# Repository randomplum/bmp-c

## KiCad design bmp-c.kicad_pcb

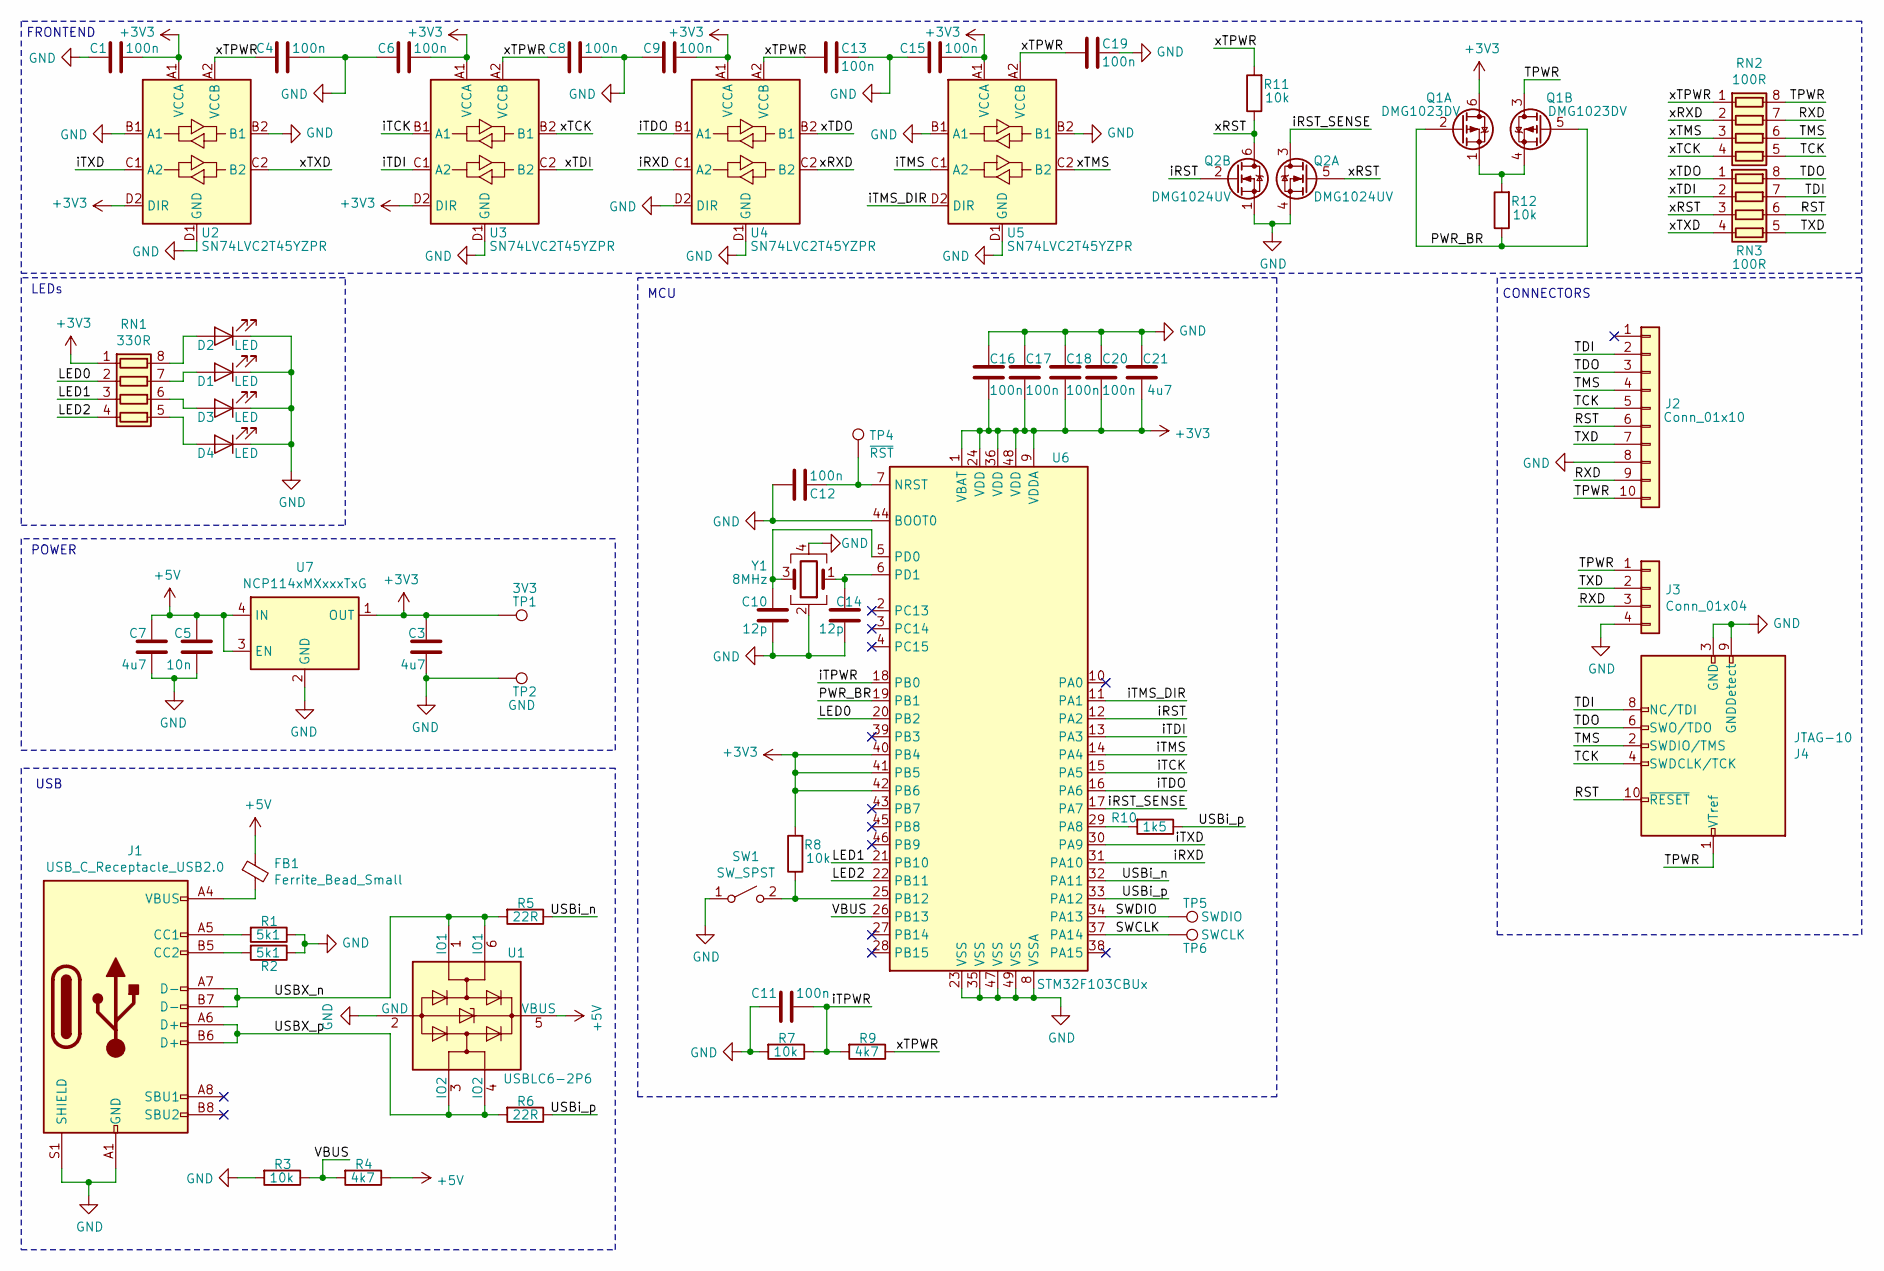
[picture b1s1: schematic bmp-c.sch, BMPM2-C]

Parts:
C1, C4, C6, C8, C9, C11, C12, C13, C15, C16, C17, C18, C19, C20: 100n; C_0402_1005Metric
C3, C7, C21: 4u7; C_0603_1608Metric
C5: 10n; C_0402_1005Metric
C10, C14: 12p; C_0402_1005Metric
D1, D2, D3, D4: LED; LED_0402_1005Metric
FB1: Ferrite_Bead_Small; Fuse_0603_1608Metric
J1: USB_C_Receptacle_USB2.0; USB_C_Receptacle_HRO_TYPE-C-31-M-12
J2: Conn_01x10; Hirose_FH12-10S-0.5SH_1x10-1MP_P0.50mm_Horizontal
J3: Conn_01x04; JST_SH_SM04B-SRSS-TB_1x04-1MP_P1.00mm_Horizontal
J4: JTAG-10; PinHeader_2x05_P1.27mm_Vertical_SMD
Q1: DMG1023DV; SOT-563
Q2: DMG1024UV; SOT-563
R1, R2: 5k1; R_0402_1005Metric
R3, R7, R8, R11, R12: 10k; R_0402_1005Metric
R4, R9: 4k7; R_0402_1005Metric
R5, R6: 22R; R_0402_1005Metric
R10: 1k5; R_0402_1005Metric
RN1: 330R; R_Array_Convex_4x0402
RN2, RN3: 100R; R_Array_Convex_4x0402
SW1: SW_SPST; SW_SPST_B3U-1000P
TP1: 3V3; TestPoint_Pad_D1.0mm
TP2: GND; TestPoint_Pad_D1.0mm
TP4: ~RST; TestPoint_Pad_D1.0mm
TP5: SWDIO; TestPoint_Pad_D1.0mm
TP6: SWCLK; TestPoint_Pad_D1.0mm
U1: USBLC6-2P6; SOT-666
U2, U3, U4, U5: SN74LVC2T45YZPR; Texas_DSBGA-8_0.9x1.9mm_Layout2x4_P0.5mm
U6: STM32F103CBUx; QFN-48-1EP_7x7mm_P0.5mm_EP5.3x5.3mm_ThermalVias
U7: NCP114xMXxxxTxG; UDFN-4_1x1mm_P0.65mm
Y1: 8MHz; Crystal_SMD_3225-4Pin_3.2x2.5mm

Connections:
+3V3: C1.1, C3.1, C6.1, C9.1, C15.1, C16.2, C17.2, C18.2, C20.2, C21.2, Q1.6 (D), R8.2, RN1.1 (R1.1), TP1.1, U2.A1 (VCCA), U2.D2 (DIR), U3.A1 (VCCA), U3.D2 (DIR), U4.A1 (VCCA), U5.A1 (VCCA), U6.1 (VBAT), U6.9 (VDDA), U6.24 (VDD), U6.36 (VDD), U6.40 (PB4), U6.41 (PB5), U6.42 (PB6), U6.48 (VDD), U7.1 (OUT)
+5V: C5.1, C7.1, FB1.1, R4.1, U1.5 (VBUS), U7.3 (EN), U7.4 (IN)
/LED0: RN1.2 (R2.1), U6.20 (PB2)
/LED1: RN1.3 (R3.1), U6.21 (PB10)
/LED2: RN1.4 (R4.1), U6.22 (PB11)
/PWR_BR: Q1.2 (G), Q1.5 (G), R12.1, U6.19 (PB1)
/RST: J2.6, J4.10 (~RESET~), RN3.6 (R3.2)
/RXD: J2.9, J3.3, RN2.7 (R2.2)
/SWCLK: TP6.1, U6.37 (PA14)
/SWDIO: TP5.1, U6.34 (PA13)
/TCK: J2.5, J4.4 (SWDCLK/TCK), RN2.5 (R4.2)
/TDI: J2.2, J4.8 (NC/TDI), RN3.7 (R2.2)
/TDO: J2.3, J4.6 (SWO/TDO), RN3.8 (R1.2)
/TMS: J2.4, J4.2 (SWDIO/TMS), RN2.6 (R3.2)
/TPWR: J2.10, J3.1, J4.1 (VTref), Q1.3 (D), RN2.8 (R1.2)
/TXD: J2.7, J3.2, RN3.5 (R4.2)
/USBX_n: J1.A7 (D-), J1.B7 (D-), R5.2, U1.1 (IO1), U1.6 (IO1)
/USBX_p: J1.A6 (D+), J1.B6 (D+), R6.2, U1.3 (IO2), U1.4 (IO2)
/USBi_n: R5.1, U6.32 (PA11)
/USBi_p: R6.1, R10.1, U6.33 (PA12)
/VBUS: R3.1, R4.2, U6.26 (PB13)
/iRST: Q2.2 (G), U6.12 (PA2)
/iRST_SENSE: Q2.3 (D), U6.17 (PA7)
/iRXD: U4.C1 (A2), U6.31 (PA10)
/iTCK: U3.B1 (A1), U6.15 (PA5)
/iTDI: U3.C1 (A2), U6.13 (PA3)
/iTDO: U4.B1 (A1), U6.16 (PA6)
/iTMS: U5.C1 (A2), U6.14 (PA4)
/iTMS_DIR: U5.D2 (DIR), U6.11 (PA1)
/iTPWR: C11.1, R7.1, R9.2, U6.18 (PB0)
/iTXD: U2.C1 (A2), U6.30 (PA9)
/xRST: Q2.5 (G), Q2.6 (D), R11.1, RN3.3 (R3.1)
/xRXD: RN2.2 (R2.1), U4.C2 (B2)
/xTCK: RN2.4 (R4.1), U3.B2 (B1)
/xTDI: RN3.2 (R2.1), U3.C2 (B2)
/xTDO: RN3.1 (R1.1), U4.B2 (B1)
/xTMS: RN2.3 (R3.1), U5.C2 (B2)
/xTPWR: C4.2, C8.2, C13.2, C19.2, R9.1, R11.2, RN2.1 (R1.1), U2.A2 (VCCB), U3.A2 (VCCB), U4.A2 (VCCB), U5.A2 (VCCB)
/xTXD: RN3.4 (R4.1), U2.C2 (B2)
GND: C1.2, C3.2, C4.1, C5.2, C6.2, C7.2, C8.1, C9.2, C10.1, C11.2, C12.2, C13.1, C14.1, C15.2, C16.1, C17.1, C18.1, C19.1, C20.1, C21.1, D1.1 (K), D2.1 (K), D3.1 (K), D4.1 (K), J1.A1 (GND), J1.A12 (GND), J1.B1 (GND), J1.B12 (GND), J1.S1 (SHIELD), J2.8, J3.4, J4.3 (GND), J4.5 (GND), J4.9 (GNDDetect), Q2.1 (S), Q2.4 (S), R1.1, R2.1, R3.2, R7.2, SW1.1 (A), TP2.1, U1.2 (GND), U2.B1 (A1), U2.B2 (B1), U2.D1 (GND), U3.D1 (GND), U4.D1 (GND), U4.D2 (DIR), U5.B1 (A1), U5.B2 (B1), U5.D1 (GND), U6.8 (VSSA), U6.23 (VSS), U6.35 (VSS), U6.44 (BOOT0), U6.47 (VSS), U6.49 (VSS), U7.2 (GND), U7.5 (GND), Y1.2, Y1.4
unnamed: C10.2, U6.5 (PD0), Y1.3
unnamed: C12.1, TP4.1, U6.7 (NRST)
unnamed: C14.2, U6.6 (PD1), Y1.1
unnamed: D1.2 (A), RN1.7 (R2.2)
unnamed: D2.2 (A), RN1.8 (R1.2)
unnamed: D3.2 (A), RN1.6 (R3.2)
unnamed: D4.2 (A), RN1.5 (R4.2)
unnamed: FB1.2, J1.A4 (VBUS), J1.A9 (VBUS), J1.B4 (VBUS), J1.B9 (VBUS)
unnamed: J1.A5 (CC1), R1.2
unnamed: J1.B5 (CC2), R2.2
unnamed: Q1.1 (S), Q1.4 (S), R12.2
unnamed: R8.1, SW1.2 (B), U6.25 (PB12)
unnamed: R10.2, U6.29 (PA8)

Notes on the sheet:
USB
POWER
LEDs
FRONTEND
MCU
CONNECTORS

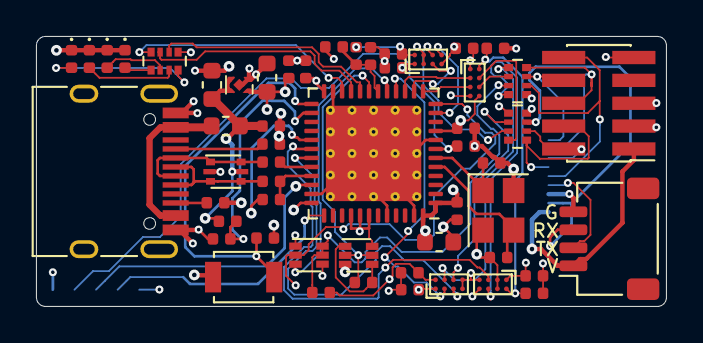
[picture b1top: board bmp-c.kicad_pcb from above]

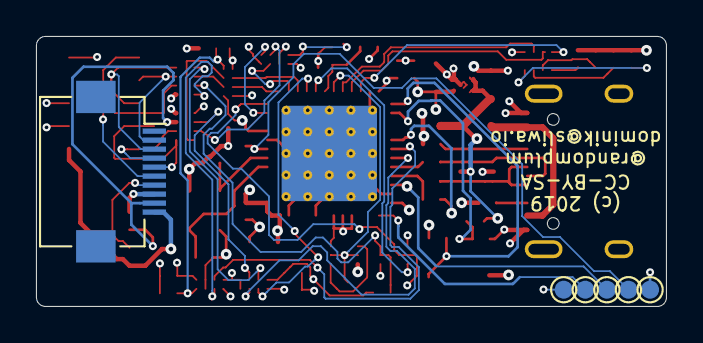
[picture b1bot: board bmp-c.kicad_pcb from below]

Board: 4 copper layers, 35.0 x 15.0 mm, 60 parts (6 on the bottom side), 53 nets.

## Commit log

2019-08-10 Schematic initial component selection
2019-08-11 Finished schematic
    changes
    -Changed resistor arrays to kicad library symbols
    -Fixed FET part numbers
    -Added multiple passive components
    -Added NCP114MX LDO
2019-08-11 Schematic style fixes
2019-08-11 Assign footprints
2019-08-11 Change level-shifter package and schematic fix
    -USBi_p was not conencted to the MCU
    -Use 74LVC2T45 in the DSBGA8 package
2019-08-11 Schematics style fixes
2019-08-11 Fix D1 footprint assigment
2019-08-11 Fix C7 footprint assigment
2019-08-11 Change STM32 footprint to include thermal vias
2019-08-11 Remove version links
    Just hardwire the version
2019-08-11 Remove C2
2019-08-11 use xTPWR as a source for the measurement divider
2019-08-11 remove SWO testpoint
2019-08-12 PCB initial p&r
2019-08-12 Fillet the corners
2019-08-15 Silkscreen improvementrs
2019-09-02 use kicad library symbol for ncp114

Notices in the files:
bmp-c.kicad_pcb:
(C) 2019 Dominik Sliwa
License: CC-BY-SA 4.0
(c) 2019
CC-BY-SA
